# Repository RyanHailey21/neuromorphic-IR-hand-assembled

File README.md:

# Neuromorphic IR Event Sensor — Rev A-THT (hand-assembly)

All through-hole re-implementation of the Rev A neuromorphic IR event sensor: no SMD parts, solderable with a basic iron. Same architecture as the SMD design spec: 4 photodiodes → TIA → temporal adaptation → ON/OFF comparators → one-shots → 8 asynchronous 3.3 V spike outputs for the Tang Nano 20K.

- **Board:** 100 × 100 mm, 2 layers, 1.6 mm FR4, 0.3 mm min track, GND pour on both layers
- **Status:** ERC 0 · DRC 0 · schematic↔PCB parity 0 · 0 unconnected
- **Fab files:** `production/neuromorphic-ir-sensor-tht-revA-THT-gerbers.zip` (upload as-is to JLCPCB/PCBWay, bare board only)
- **BOM:** `production/neuromorphic-ir-sensor-tht-BOM.csv` · **Schematic:** `docs/schematic.pdf` · **Assembly drawing:** `docs/assembly_top.pdf`

## Changes from the SMD spec

| Function | SMD Rev A | Rev A-THT | Effect |
|---|---|---|---|
| TIA ×4 | OPA381 | 2× **MCP6022-I/P** (dual, DIP-8) | RF/CF unchanged (18k / 47 pF); ~188 kHz BW, large phase margin |
| Comparators ×8 | 4× TLV3202 | 4× **MCP6542-I/P** (dual, DIP-8) | ~4 µs response, irrelevant vs 2.2 ms adaptation |
| One-shots ×8 | 8× 74LVC1G123 | 4× **74HC123** (dual, DIP-16) | 18k / 12 nF ≈ 100 µs (K≈0.45) — tune on bench |
| VREF | REF3312 1.250 V | **LM385BZ-1.2** 1.235 V + 4.7k | Thresholds ≈ +40.6 / −39.7 mV |
| LED switch | AO3400A | **PN2222A** + 1k base | ~22 mA LED current with 82 Ω |
| Photodiodes | VBPW34FASR | **OSRAM BPW 34 F** (daylight filter) | Same die, THT |

The FPGA connector follows the spec (keyed 2×5: GND, 3V3, SPIKE_ON/OFF × 4). The AER / 2×10 pinout in the old README had no driving circuitry and was dropped.

## Connectors

| Ref | Pins |
|---|---|
| J1 FPGA (2×5 box) | 1 GND · 2 3V3 · 3 ON_TL · 4 OFF_TL · 5 ON_TR · 6 OFF_TR · 7 ON_BL · 8 OFF_BL · 9 ON_BR · 10 OFF_BR |
| J2 DEBUG | 1 GND · 2 VREF · 3–6 VPHOTO_TL/TR/BL/BR (via 100 Ω) |
| J3 LED_EN | 1 3V3 · 2 LED_EN · 3 GND — jumper 1-2 = LED on, 2-3 = off, or drive pin 2 from FPGA |
| J4 RAW_PROBE | 1 GND · 2–9 RAW_ON/OFF_TL, TR, BL, BR |
| J5 EVENT_PROBE | 1 GND · 2 3V3 · 3 3V3A · 4 VREF · 5 VTH_ON · 6 VTH_OFF · 7–10 VEVENT_TL/TR/BL/BR |

## Assembly notes

- Buy 6× DIP-8 and 4× DIP-16 sockets; fit ICs last.
- Solder lowest parts first: resistors → ceramic caps → sockets → TO-92 → electrolytics → headers → photodiodes/LED.
- **Polarity:** photodiode cathode (marked side) → square pad; LED1 cathode (flat) → square pad; electrolytic + marked on silk; U1/Q1 flat side per silk.
- R18–R21 (1 MΩ hysteresis) are **DNP** — fit only if comparators chatter.
- Tuning parts (adaptation R/C, one-shot R/C, thresholds, RLED) can be fitted in machined-pin socket strips for tool-free swapping.
- Keep the photodiode cluster area clear for the M12 lens housing.

## Regenerating (headless)

Everything is generated from `.companion/scripts/design.py` (netlist source of truth). With KiCad closed:

```bash
python .companion/scripts/gen_schematic.py --force
"C:/Program Files/KiCad/10.0/bin/python.exe" .companion/scripts/gen_pcb.py --force
python .companion/scripts/setup_rules.py
# autoroute (kicad-companion autoroute_board / Freerouting), then:
"C:/Program Files/KiCad/10.0/bin/python.exe" .companion/scripts/finalize_pcb.py
python .companion/scripts/setup_rules.py
```

Close KiCad before regenerating: it rewrites the `.kicad_pro` from memory on exit and drops the net classes.

## Open items

- Re-run SPICE with Microchip's MCP6022 / MCP6542 vendor models (not yet in the repo).
- Bench-trim the 74HC123 pulse width (K varies with supply voltage).
- The TIA input nets (photodiode + RF + CF) are autorouted at 22–36 mm total length, well above the spec's 2–8 mm photodiode→op-amp target. The op-amps sit back from the cluster to leave room for the lens housing. Worth a manual tidy-up in KiCad if noise turns out to be a problem on the bench.

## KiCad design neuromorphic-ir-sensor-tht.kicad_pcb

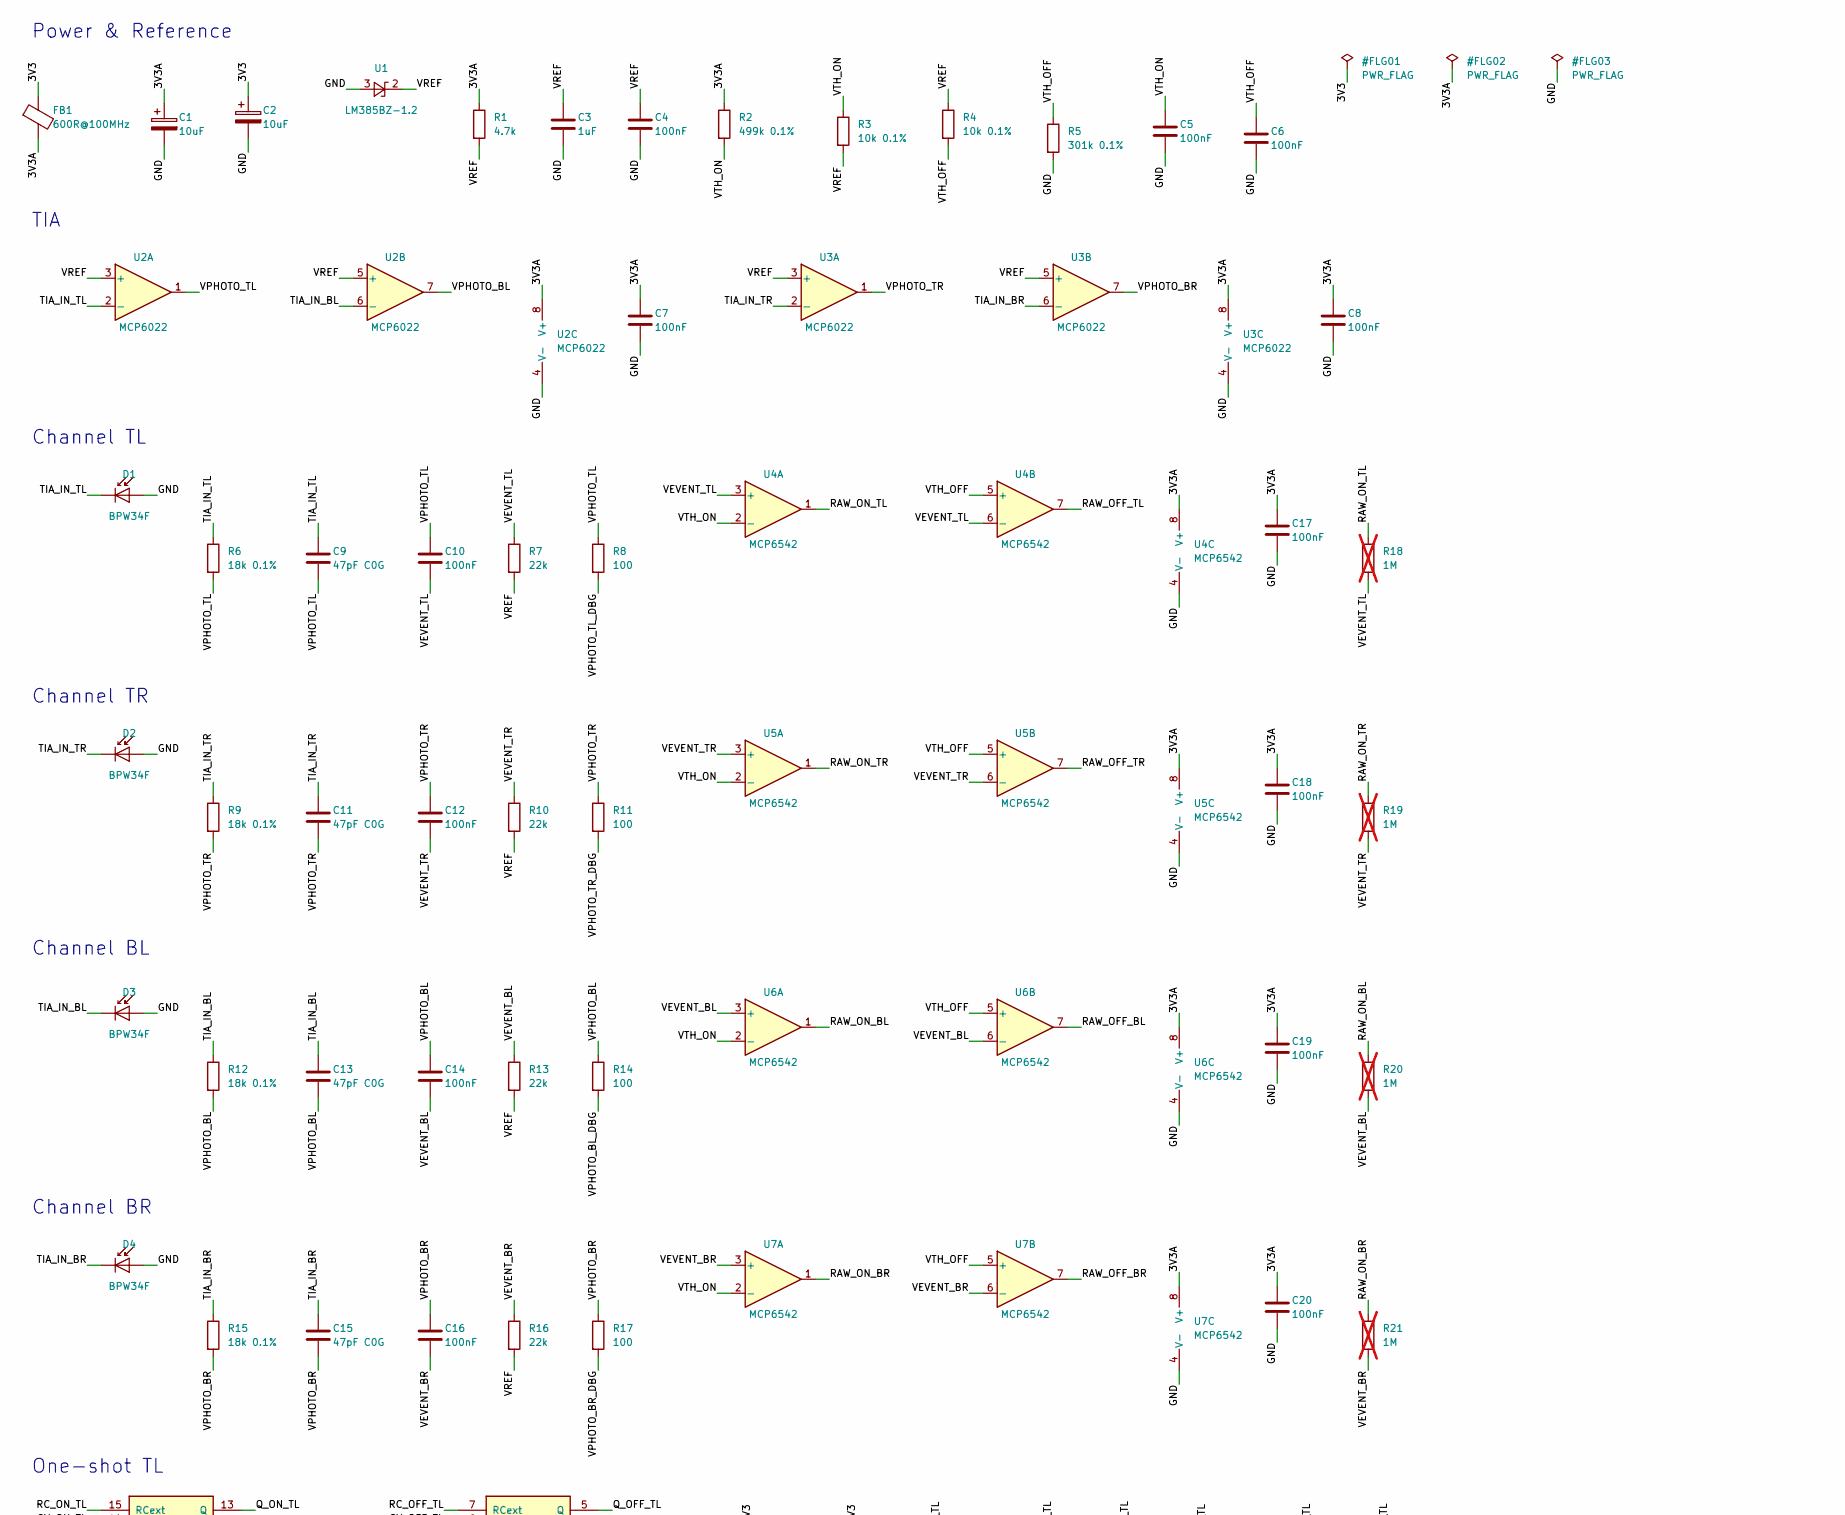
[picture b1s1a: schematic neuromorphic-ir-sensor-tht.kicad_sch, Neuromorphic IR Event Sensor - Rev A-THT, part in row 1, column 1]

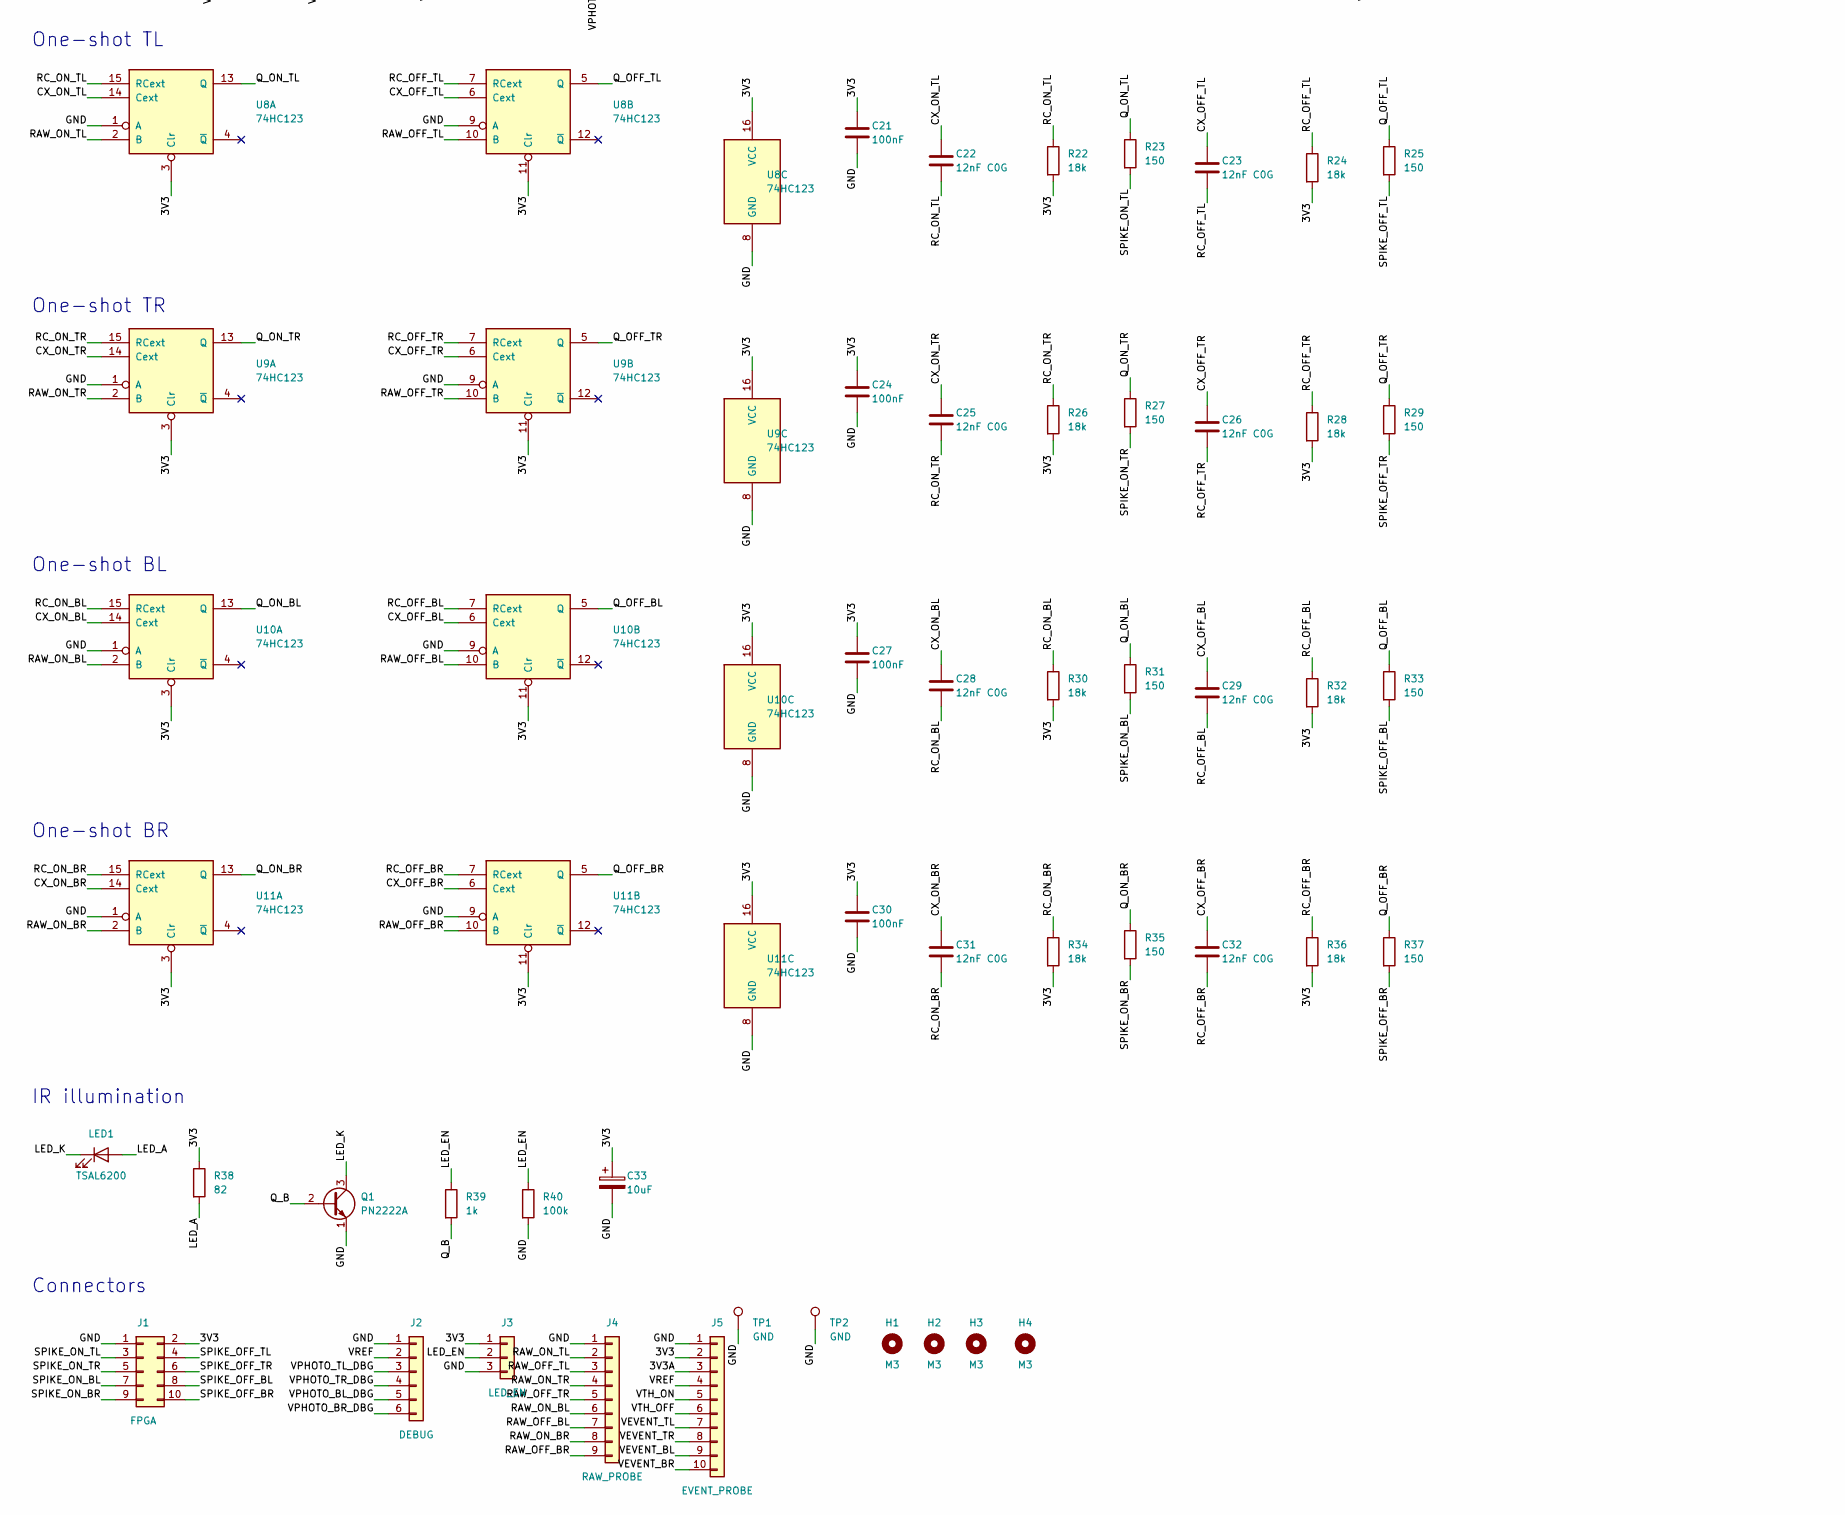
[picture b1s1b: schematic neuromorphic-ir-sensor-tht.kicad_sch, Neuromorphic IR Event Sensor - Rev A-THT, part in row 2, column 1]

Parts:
C1, C2, C33: 10uF; CP_Radial_D5.0mm_P2.00mm; MPN 10uF 16V radial electrolytic
C3: 1uF; C_Disc_D5.0mm_W2.5mm_P5.00mm; MPN 1uF X7R radial
C4, C5, C6, C7, C8, C10, C12, C14, C16, C17, C18, C19, C20, C21, C24, C27, C30: 100nF; C_Disc_D5.0mm_W2.5mm_P5.00mm
C9, C11, C13, C15: 47pF C0G; C_Disc_D5.0mm_W2.5mm_P5.00mm; MPN 47pF C0G radial
C22, C23, C25, C26, C28, C29, C31, C32: 12nF C0G; C_Disc_D5.0mm_W2.5mm_P5.00mm; MPN 12nF C0G radial or film
D1, D2, D3, D4: BPW34F; Osram_DIL2_4.3x4.65mm_P5.08mm; MPN ams OSRAM BPW 34 F (THT, daylight filte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
FB1: 600R@100MHz; L_Axial_L5.3mm_D2.2mm_P7.62mm_Horizontal_Vishay_IM-1; MPN Axial ferrite bead (e.g. Fair-Rite 2743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
H1, H2, H3, H4: M3; MountingHole_3.2mm_M3
J1: FPGA; IDC-Header_2x05_P2.54mm_Vertical; MPN 2x5 2.54mm shrouded box header
J2: DEBUG; PinHeader_1x06_P2.54mm_Vertical
J3: LED_EN; PinHeader_1x03_P2.54mm_Vertical
J4: RAW_PROBE; PinHeader_1x09_P2.54mm_Vertical
J5: EVENT_PROBE; PinHeader_1x10_P2.54mm_Vertical
LED1: TSAL6200; LED_D5.0mm_IRGrey; MPN Vishay TSAL6200
Q1: PN2222A; TO-92_Inline_Wide; MPN PN2222A
R1: 4.7k; R_Axial_DIN0207_L6.3mm_D2.5mm_P7.62mm_Horizontal
R2: 499k 0.1%; R_Axial_DIN0207_L6.3mm_D2.5mm_P7.62mm_Horizontal
R3, R4: 10k 0.1%; R_Axial_DIN0207_L6.3mm_D2.5mm_P7.62mm_Horizontal
R5: 301k 0.1%; R_Axial_DIN0207_L6.3mm_D2.5mm_P7.62mm_Horizontal
R6, R9, R12, R15: 18k 0.1%; R_Axial_DIN0207_L6.3mm_D2.5mm_P7.62mm_Horizontal
R7, R10, R13, R16: 22k; R_Axial_DIN0207_L6.3mm_D2.5mm_P7.62mm_Horizontal
R8, R11, R14, R17: 100; R_Axial_DIN0207_L6.3mm_D2.5mm_P7.62mm_Horizontal
R18, R19, R20, R21: 1M; R_Axial_DIN0207_L6.3mm_D2.5mm_P7.62mm_Horizontal; not fitted
R22, R24, R26, R28, R30, R32, R34, R36: 18k; R_Axial_DIN0207_L6.3mm_D2.5mm_P7.62mm_Horizontal
R23, R25, R27, R29, R31, R33, R35, R37: 150; R_Axial_DIN0207_L6.3mm_D2.5mm_P7.62mm_Horizontal
R38: 82; R_Axial_DIN0207_L6.3mm_D2.5mm_P7.62mm_Horizontal
R39: 1k; R_Axial_DIN0207_L6.3mm_D2.5mm_P7.62mm_Horizontal
R40: 100k; R_Axial_DIN0207_L6.3mm_D2.5mm_P7.62mm_Horizontal
TP1, TP2: GND; TestPoint_Keystone_5000-5004_Miniature
U1: LM385BZ-1.2; TO-92_Inline_Wide; MPN LM385BZ-1.2
U2, U3: MCP6022; DIP-8_W7.62mm_Socket; MPN MCP6022-I/P
U4, U5, U6, U7: MCP6542; DIP-8_W7.62mm_Socket; MPN MCP6542-I/P
U8, U9, U10, U11: 74HC123; DIP-16_W7.62mm_Socket; MPN 74HC123 (SN74HC123N / 74HC123N)

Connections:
/3V3: C2.1, C21.1, C24.1, C27.1, C30.1, C33.1, FB1.1, J1.2, J3.1, J5.2, R22.2, R24.2, R26.2, R28.2, R30.2, R32.2, R34.2, R36.2, R38.1, U8.3 (Clr), U8.11 (Clr), U8.16 (VCC), U9.3 (Clr), U9.11 (Clr), U9.16 (VCC), U10.3 (Clr), U10.11 (Clr), U10.16 (VCC), U11.3 (Clr), U11.11 (Clr), U11.16 (VCC)
/3V3A: C1.1, C7.1, C8.1, C17.1, C18.1, C19.1, C20.1, FB1.2, J5.3, R1.1, R2.1, U2.8 (V+), U3.8 (V+), U4.8 (V+), U5.8 (V+), U6.8 (V+), U7.8 (V+)
/CX_OFF_BL: C29.1, U10.6 (Cext)
/CX_OFF_BR: C32.1, U11.6 (Cext)
/CX_OFF_TL: C23.1, U8.6 (Cext)
/CX_OFF_TR: C26.1, U9.6 (Cext)
/CX_ON_BL: C28.1, U10.14 (Cext)
/CX_ON_BR: C31.1, U11.14 (Cext)
/CX_ON_TL: C22.1, U8.14 (Cext)
/CX_ON_TR: C25.1, U9.14 (Cext)
/GND: C1.2, C2.2, C3.2, C4.2, C5.2, C6.2, C7.2, C8.2, C17.2, C18.2, C19.2, C20.2, C21.2, C24.2, C27.2, C30.2, C33.2, D1.2 (A), D2.2 (A), D3.2 (A), D4.2 (A), J1.1, J2.1, J3.3, J4.1, J5.1, Q1.1 (E), R5.2, R40.2, TP1.1, TP2.1, U1.3 (A), U2.4 (V-), U3.4 (V-), U4.4 (V-), U5.4 (V-), U6.4 (V-), U7.4 (V-), U8.1 (A), U8.8 (GND), U8.9 (A), U9.1 (A), U9.8 (GND), U9.9 (A), U10.1 (A), U10.8 (GND), U10.9 (A), U11.1 (A), U11.8 (GND), U11.9 (A)
/LED_A: LED1.2 (A), R38.2
/LED_EN: J3.2, R39.1, R40.1
/LED_K: LED1.1 (K), Q1.3 (C)
/Q_B: Q1.2 (B), R39.2
/Q_OFF_BL: R33.1, U10.5 (Q)
/Q_OFF_BR: R37.1, U11.5 (Q)
/Q_OFF_TL: R25.1, U8.5 (Q)
/Q_OFF_TR: R29.1, U9.5 (Q)
/Q_ON_BL: R31.1, U10.13 (Q)
/Q_ON_BR: R35.1, U11.13 (Q)
/Q_ON_TL: R23.1, U8.13 (Q)
/Q_ON_TR: R27.1, U9.13 (Q)
/RAW_OFF_BL: J4.7, U6.7, U10.10 (B)
/RAW_OFF_BR: J4.9, U7.7, U11.10 (B)
/RAW_OFF_TL: J4.3, U4.7, U8.10 (B)
/RAW_OFF_TR: J4.5, U5.7, U9.10 (B)
/RAW_ON_BL: J4.6, R20.1, U6.1, U10.2 (B)
/RAW_ON_BR: J4.8, R21.1, U7.1, U11.2 (B)
/RAW_ON_TL: J4.2, R18.1, U4.1, U8.2 (B)
/RAW_ON_TR: J4.4, R19.1, U5.1, U9.2 (B)
/RC_OFF_BL: C29.2, R32.1, U10.7 (RCext)
/RC_OFF_BR: C32.2, R36.1, U11.7 (RCext)
/RC_OFF_TL: C23.2, R24.1, U8.7 (RCext)
/RC_OFF_TR: C26.2, R28.1, U9.7 (RCext)
/RC_ON_BL: C28.2, R30.1, U10.15 (RCext)
/RC_ON_BR: C31.2, R34.1, U11.15 (RCext)
/RC_ON_TL: C22.2, R22.1, U8.15 (RCext)
/RC_ON_TR: C25.2, R26.1, U9.15 (RCext)
/SPIKE_OFF_BL: J1.8, R33.2
/SPIKE_OFF_BR: J1.10, R37.2
/SPIKE_OFF_TL: J1.4, R25.2
/SPIKE_OFF_TR: J1.6, R29.2
/SPIKE_ON_BL: J1.7, R31.2
/SPIKE_ON_BR: J1.9, R35.2
/SPIKE_ON_TL: J1.3, R23.2
/SPIKE_ON_TR: J1.5, R27.2
/TIA_IN_BL: C13.1, D3.1 (K), R12.1, U2.6 (-)
/TIA_IN_BR: C15.1, D4.1 (K), R15.1, U3.6 (-)
/TIA_IN_TL: C9.1, D1.1 (K), R6.1, U2.2 (-)
/TIA_IN_TR: C11.1, D2.1 (K), R9.1, U3.2 (-)
/VEVENT_BL: C14.2, J5.9, R13.1, R20.2, U6.3 (+), U6.6 (-)
/VEVENT_BR: C16.2, J5.10, R16.1, R21.2, U7.3 (+), U7.6 (-)
/VEVENT_TL: C10.2, J5.7, R7.1, R18.2, U4.3 (+), U4.6 (-)
/VEVENT_TR: C12.2, J5.8, R10.1, R19.2, U5.3 (+), U5.6 (-)
/VPHOTO_BL: C13.2, C14.1, R12.2, R14.1, U2.7
/VPHOTO_BL_DBG: J2.5, R14.2
/VPHOTO_BR: C15.2, C16.1, R15.2, R17.1, U3.7
/VPHOTO_BR_DBG: J2.6, R17.2
/VPHOTO_TL: C9.2, C10.1, R6.2, R8.1, U2.1
/VPHOTO_TL_DBG: J2.3, R8.2
/VPHOTO_TR: C11.2, C12.1, R9.2, R11.1, U3.1
/VPHOTO_TR_DBG: J2.4, R11.2
/VREF: C3.1, C4.1, J2.2, J5.4, R1.2, R3.2, R4.1, R7.2, R10.2, R13.2, R16.2, U1.2 (K), U2.3 (+), U2.5 (+), U3.3 (+), U3.5 (+)
/VTH_OFF: C6.1, J5.6, R4.2, R5.1, U4.5 (+), U5.5 (+), U6.5 (+), U7.5 (+)
/VTH_ON: C5.1, J5.5, R2.2, R3.1, U4.2 (-), U5.2 (-), U6.2 (-), U7.2 (-)

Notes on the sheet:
Power & Reference
TIA
Channel TL
Channel TR
Channel BL
Channel BR
One-shot TL
One-shot TR
One-shot BL
One-shot BR
IR illumination
Connectors
Neuromorphic IR Event Sensor - Rev A-THT (all through-hole, hand-assemblable). Single source of truth for the netlist. gen_schematic.py turns this into the KiCad schematic; the PCB is then populated from the schematic netlist. Deviations from docs/DESIGN_SPECIFICATION.md (SMD Rev A), forced by THT 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

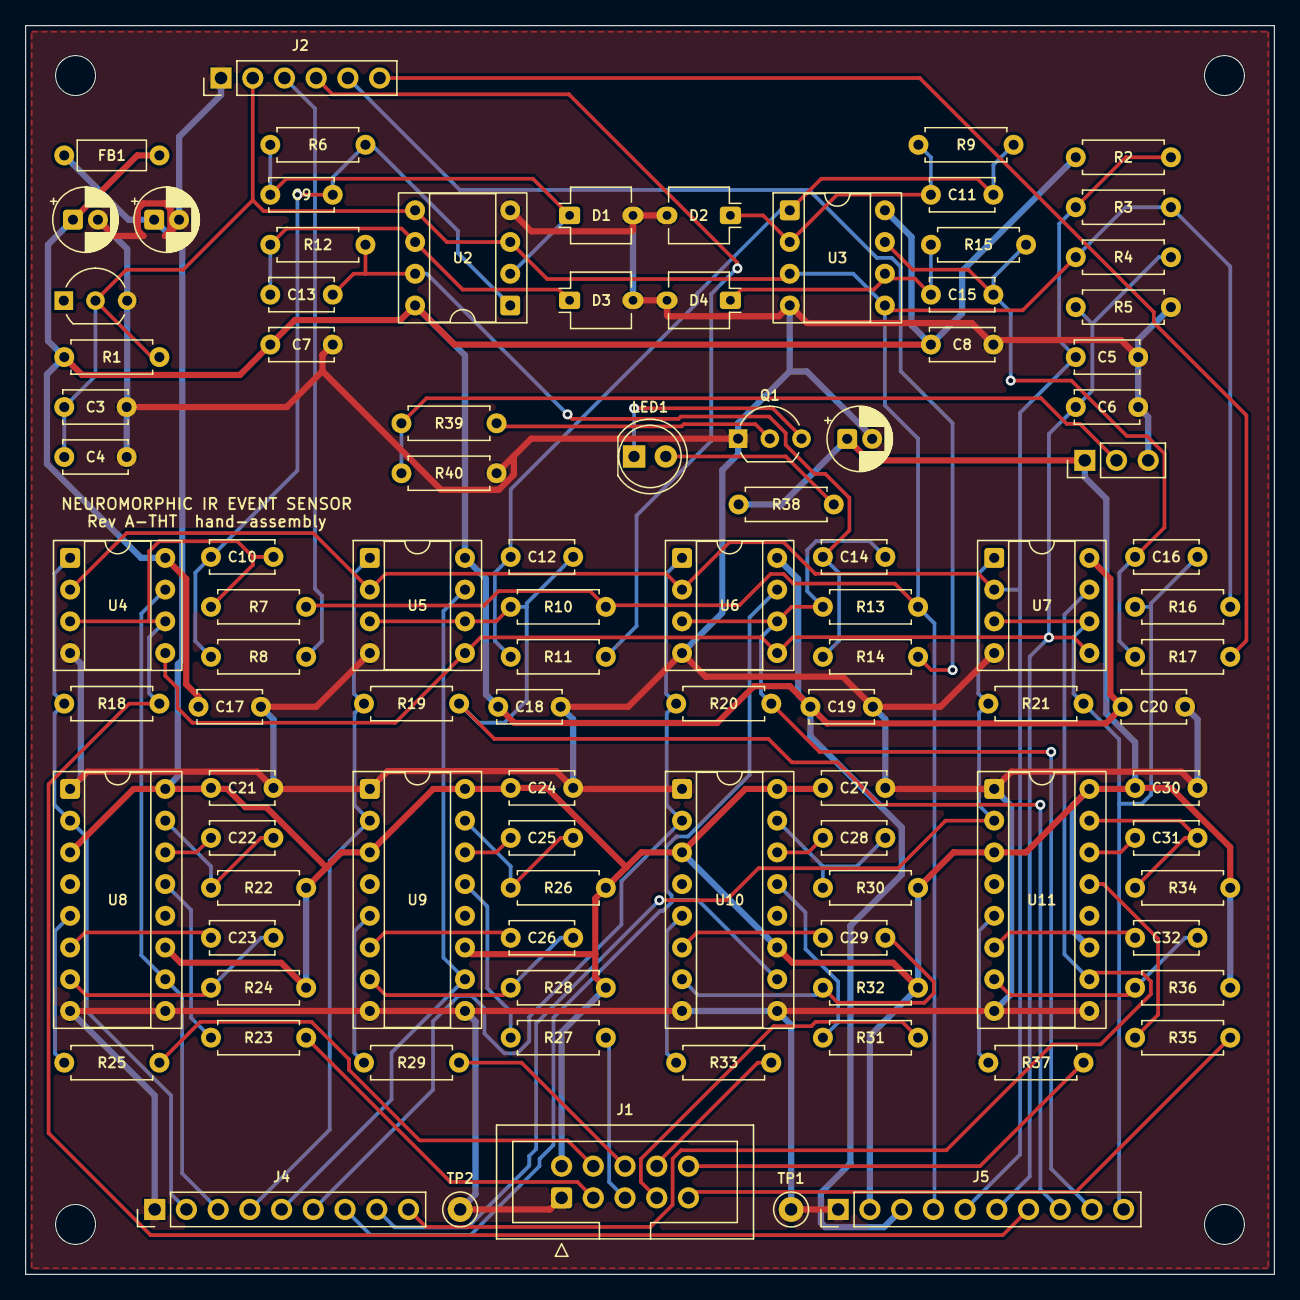
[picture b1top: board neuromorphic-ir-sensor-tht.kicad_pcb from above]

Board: 2 copper layers, 100.0 x 100.0 mm, 102 parts (0 on the bottom side), 66 nets.

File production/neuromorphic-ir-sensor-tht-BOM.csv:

"Qty","Value","References","Part / MPN","Function","Footprint","DNP"
"3","10uF","C1,C2,C33","10uF 16V radial electrolytic","Analog bulk,LED local bulk,Logic / one-shot bulk","Capacitor_THT:CP_Radial_D5.0mm_P2.00mm",""
"1","1uF","C3","1uF X7R radial","Reference decoupling","Capacitor_THT:C_Disc_D5.0mm_W2.5mm_P5.00mm",""
"17","100nF","C4-C8,C10,C12,C14,C16-C21,C24,C27,C30","","Adaptation CA (swap 47n/220n),Reference decoupling,Threshold filter,U10 decoupling,U11 decoupling,U2 decoupling,U3 decoupling,U4 decoupling,U5 decoupling,U6 decoupling,U7 decoupling,U8 decoupling,U9 decoupling","Capacitor_THT:C_Disc_D5.0mm_W2.5mm_P5.00mm",""
"4","47pF C0G","C9,C11,C13,C15","47pF C0G radial","TIA feedback CF","Capacitor_THT:C_Disc_D5.0mm_W2.5mm_P5.00mm",""
"8","12nF C0G","C22,C23,C25,C26,C28,C29,C31,C32","12nF C0G radial or film","One-shot timing C","Capacitor_THT:C_Disc_D5.0mm_W2.5mm_P5.00mm",""
"4","BPW34F","D1-D4","ams OSRAM BPW 34 F (THT, daylight filter); alt Vishay BPW34","IR photodiode BL (cathode to TIA input),IR photodiode BR (cathode to TIA input),IR photodiode TL (cathode to TIA input),IR photodiode TR (cathode to TIA input)","OptoDevice:Osram_DIL2_4.3x4.65mm_P5.08mm",""
"1","600R@100MHz","FB1","Axial ferrite bead (e.g. Fair-Rite 2743001112)","Analog rail filter bead","Inductor_THT:L_Axial_L5.3mm_D2.2mm_P7.62mm_Horizontal_Vishay_IM-1",""
"1","FPGA","J1","2x5 2.54mm shrouded box header","Keyed 2x5 event header to Tang Nano 20K","Connector_IDC:IDC-Header_2x05_P2.54mm_Vertical",""
"1","DEBUG","J2","","Analog debug header","Connector_PinHeader_2.54mm:PinHeader_1x06_P2.54mm_Vertical",""
"1","LED_EN","J3","","Jumper 1-2 = LED on, 2-3 = off, or drive pin 2 from FPGA","Connector_PinHeader_2.54mm:PinHeader_1x03_P2.54mm_Vertical",""
"1","RAW_PROBE","J4","","Raw comparator probe header","Connector_PinHeader_2.54mm:PinHeader_1x09_P2.54mm_Vertical",""
"1","EVENT_PROBE","J5","","Rail / threshold / event-node probe header","Connector_PinHeader_2.54mm:PinHeader_1x10_P2.54mm_Vertical",""
"1","TSAL6200","LED1","Vishay TSAL6200","940 nm IR emitter","LED_THT:LED_D5.0mm_IRGrey",""
"1","PN2222A","Q1","PN2222A","LED low-side switch","Package_TO_SOT_THT:TO-92_Inline_Wide",""
"1","4.7k","R1","","Reference bias ~0.44 mA","Resistor_THT:R_Axial_DIN0207_L6.3mm_D2.5mm_P7.62mm_Horizontal",""
"1","499k 0.1%","R2","","ON threshold upper","Resistor_THT:R_Axial_DIN0207_L6.3mm_D2.5mm_P7.62mm_Horizontal",""
"2","10k 0.1%","R3,R4","","OFF threshold upper,ON threshold lower","Resistor_THT:R_Axial_DIN0207_L6.3mm_D2.5mm_P7.62mm_Horizontal",""
"1","301k 0.1%","R5","","OFF threshold lower","Resistor_THT:R_Axial_DIN0207_L6.3mm_D2.5mm_P7.62mm_Horizontal",""
"4","18k 0.1%","R6,R9,R12,R15","","TIA feedback RF","Resistor_THT:R_Axial_DIN0207_L6.3mm_D2.5mm_P7.62mm_Horizontal",""
"4","22k","R7,R10,R13,R16","","Adaptation RA (swap 10k/47k)","Resistor_THT:R_Axial_DIN0207_L6.3mm_D2.5mm_P7.62mm_Horizontal",""
"4","100","R8,R11,R14,R17","","Debug header series R","Resistor_THT:R_Axial_DIN0207_L6.3mm_D2.5mm_P7.62mm_Horizontal",""
"4","1M","R18-R21","","Optional ON hysteresis (DNP)","Resistor_THT:R_Axial_DIN0207_L6.3mm_D2.5mm_P7.62mm_Horizontal","DNP"
"8","18k","R22,R24,R26,R28,R30,R32,R34,R36","","One-shot timing R (~100 us)","Resistor_THT:R_Axial_DIN0207_L6.3mm_D2.5mm_P7.62mm_Horizontal",""
"8","150","R23,R25,R27,R29,R31,R33,R35,R37","","Spike series R","Resistor_THT:R_Axial_DIN0207_L6.3mm_D2.5mm_P7.62mm_Horizontal",""
"1","82","R38","","LED current (~22 mA) - tuning 68/100/150","Resistor_THT:R_Axial_DIN0207_L6.3mm_D2.5mm_P7.62mm_Horizontal",""
"1","1k","R39","","Base resistor","Resistor_THT:R_Axial_DIN0207_L6.3mm_D2.5mm_P7.62mm_Horizontal",""
"1","100k","R40","","LED_EN pulldown","Resistor_THT:R_Axial_DIN0207_L6.3mm_D2.5mm_P7.62mm_Horizontal",""
"2","GND","TP1,TP2","","Scope ground loop","TestPoint:TestPoint_Keystone_5000-5004_Miniature",""
"1","LM385BZ-1.2","U1","LM385BZ-1.2","1.235 V shunt reference (VREF)","Package_TO_SOT_THT:TO-92_Inline_Wide",""
"2","MCP6022","U2,U3","MCP6022-I/P","Dual RRIO CMOS op-amp (TIA)","Package_DIP:DIP-8_W7.62mm_Socket",""
"4","MCP6542","U4-U7","MCP6542-I/P","Dual push-pull comparator, ON (A) / OFF (B)","Package_DIP:DIP-8_W7.62mm_Socket",""
"4","74HC123","U8-U11","74HC123 (SN74HC123N / 74HC123N)","Dual retriggerable monostable, ON (A) / OFF (B)","Package_DIP:DIP-16_W7.62mm_Socket",""

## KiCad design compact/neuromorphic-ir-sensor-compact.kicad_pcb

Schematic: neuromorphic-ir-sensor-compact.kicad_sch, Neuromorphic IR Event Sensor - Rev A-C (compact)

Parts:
C1, C2, C38: 10uF; C_0402_1005Metric; MPN GRM155R60J106ME15D
C3, C5, C6, C7, C8, C9, C11, C13, C15, C17, C18, C19, C20, C21, C22, C24, C26, C28, C30, C32, C34, C36: 100nF; C_0201_0603Metric; MPN GRM033R71A104KA01D
C4: 1uF; C_0201_0603Metric; MPN GRM033R60J105MEA2D
C10, C12, C14, C16: 47pF; C_0201_0603Metric; MPN GRM0335C1H470JA01D
C23, C25, C27, C29, C31, C33, C35, C37: 1nF; C_0201_0603Metric; MPN GRM0335C1H102JA01D
D1, D2, D3, D4: BPW 34 FAS; Osram_BPW34S-SMD; MPN BPW 34 FAS
FB1: 600R@100MHz; L_0402_1005Metric; MPN BLM15AG601SN1D
H1, H2: M2; MountingHole_2.2mm_M2
J1: FPGA; PinHeader_2x05_P1.27mm_Vertical_SMD; MPN 2x5 1.27mm SMD pin header, gold
JP1: LED_EN; SolderJumper-3_P1.3mm_Bridged12_Pad1.0x1.5mm
LED1: TSAL6200; LED_D5.0mm_IRGrey; MPN TSAL6200
Q1: AO3400A; SOT-23; MPN AO3400A
R1: 499k 0.1%; R_0402_1005Metric; MPN 499k 0.1% 0402 thin film
R2, R3: 10k 0.1%; R_0402_1005Metric; MPN 10k 0.1% 0402 thin film
R4: 301k 0.1%; R_0402_1005Metric; MPN 301k 0.1% 0402 thin film
R5, R7, R9, R11: 18k 0.1%; R_0201_0603Metric; MPN 18k 0.1% 0201 thin film
R6, R8, R10, R12: 22k; R_0201_0603Metric; MPN 22k 0201 thick film 1%
R13, R14, R15, R16: 1M; R_0201_0603Metric; MPN 1M 0201 thick film 1%; not fitted
R17, R19, R21, R23, R25, R27, R29, R31, R35: 100k; R_0201_0603Metric; MPN 100k 0201 thick film 1%
R18, R20, R22, R24, R26, R28, R30, R32: 150; R_0201_0603Metric; MPN 150 0201 thick film 1%
R33: 82; R_0402_1005Metric; MPN 82R 0402 1% (62.5 mW)
R34: 100; R_0201_0603Metric; MPN 100 0201 thick film 1%
TP1: 3V3A; TestPoint_Pad_D1.0mm
TP2: GND; TestPoint_Pad_D1.0mm
TP3: VREF; TestPoint_Pad_D1.0mm
TP4: VTH_ON; TestPoint_Pad_D1.0mm
TP5: VTH_OFF; TestPoint_Pad_D1.0mm
TP6: LED_EN; TestPoint_Pad_D1.0mm
TP7: VPHOTO_TL; TestPoint_Pad_D1.0mm
TP8: VPHOTO_TR; TestPoint_Pad_D1.0mm
TP9: VPHOTO_BL; TestPoint_Pad_D1.0mm
TP10: VPHOTO_BR; TestPoint_Pad_D1.0mm
TP11: VEVENT_TL; TestPoint_Pad_D1.0mm
TP12: VEVENT_TR; TestPoint_Pad_D1.0mm
TP13: VEVENT_BL; TestPoint_Pad_D1.0mm
TP14: VEVENT_BR; TestPoint_Pad_D1.0mm
TP15: RAW_ON_TL; TestPoint_Pad_D1.0mm
TP16: RAW_OFF_TL; TestPoint_Pad_D1.0mm
TP17: RAW_ON_TR; TestPoint_Pad_D1.0mm
TP18: RAW_OFF_TR; TestPoint_Pad_D1.0mm
TP19: RAW_ON_BL; TestPoint_Pad_D1.0mm
TP20: RAW_OFF_BL; TestPoint_Pad_D1.0mm
TP21: RAW_ON_BR; TestPoint_Pad_D1.0mm
TP22: RAW_OFF_BR; TestPoint_Pad_D1.0mm
U1: REF3312AIDCKR; SOT-323_SC-70; MPN REF3312AIDCKR
U2, U3: OPA2381AIDRBR; VSON-8-1EP_3x3mm_P0.65mm_EP1.65x2.4mm; MPN OPA2381AIDRBR
U4, U5, U6, U7: TLV3202AIDGKR; VSSOP-8_3x3mm_P0.65mm; MPN TLV3202AIDGKR
U8, U9, U10, U11, U12, U13, U14, U15: SN74LVC1G123DCUR; VSSOP-8_2.3x2mm_P0.5mm; MPN SN74LVC1G123DCUR

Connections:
/3V3: C2.1, C22.1, C24.1, C26.1, C28.1, C30.1, C32.1, C34.1, C36.1, C38.1, FB1.1, J1.2, JP1.1 (A), R17.2, R19.2, R21.2, R23.2, R25.2, R27.2, R29.2, R31.2, R33.1, U8.3 (~CLR), U8.8 (VCC), U9.3 (~CLR), U9.8 (VCC), U10.3 (~CLR), U10.8 (VCC), U11.3 (~CLR), U11.8 (VCC), U12.3 (~CLR), U12.8 (VCC), U13.3 (~CLR), U13.8 (VCC), U14.3 (~CLR), U14.8 (VCC), U15.3 (~CLR), U15.8 (VCC)
/3V3A: C1.1, C3.1, C8.1, C9.1, C18.1, C19.1, C20.1, C21.1, FB1.2, R1.1, TP1.1, U1.1 (IN), U2.8 (V+), U3.8 (V+), U4.8 (V+), U5.8 (V+), U6.8 (V+), U7.8 (V+)
/CX_OFF_BL: C33.1, U13.6 (Cext)
/CX_OFF_BR: C37.1, U15.6 (Cext)
/CX_OFF_TL: C25.1, U9.6 (Cext)
/CX_OFF_TR: C29.1, U11.6 (Cext)
/CX_ON_BL: C31.1, U12.6 (Cext)
/CX_ON_BR: C35.1, U14.6 (Cext)
/CX_ON_TL: C23.1, U8.6 (Cext)
/CX_ON_TR: C27.1, U10.6 (Cext)
/GND: C1.2, C2.2, C3.2, C4.2, C5.2, C6.2, C7.2, C8.2, C9.2, C18.2, C19.2, C20.2, C21.2, C22.2, C24.2, C26.2, C28.2, C30.2, C32.2, C34.2, C36.2, C38.2, D1.2 (A), D2.2 (A), D3.2 (A), D4.2 (A), J1.1, JP1.3 (B), Q1.2 (S), R4.2, R35.2, TP2.1, U1.3 (GND), U2.4 (V-), U2.9 (EP), U3.4 (V-), U3.9 (EP), U4.4 (V-), U5.4 (V-), U6.4 (V-), U7.4 (V-), U8.1 (~A), U8.4 (GND), U9.1 (~A), U9.4 (GND), U10.1 (~A), U10.4 (GND), U11.1 (~A), U11.4 (GND), U12.1 (~A), U12.4 (GND), U13.1 (~A), U13.4 (GND), U14.1 (~A), U14.4 (GND), U15.1 (~A), U15.4 (GND)
/LED_A: LED1.2 (A), R33.2
/LED_EN: JP1.2 (C), R34.1, TP6.1
/LED_K: LED1.1 (K), Q1.3 (D)
/Q_G: Q1.1 (G), R34.2, R35.1
/Q_OFF_BL: R28.1, U13.5 (Q)
/Q_OFF_BR: R32.1, U15.5 (Q)
/Q_OFF_TL: R20.1, U9.5 (Q)
/Q_OFF_TR: R24.1, U11.5 (Q)
/Q_ON_BL: R26.1, U12.5 (Q)
/Q_ON_BR: R30.1, U14.5 (Q)
/Q_ON_TL: R18.1, U8.5 (Q)
/Q_ON_TR: R22.1, U10.5 (Q)
/RAW_OFF_BL: TP20.1, U6.7, U13.2 (B)
/RAW_OFF_BR: TP22.1, U7.7, U15.2 (B)
/RAW_OFF_TL: TP16.1, U4.7, U9.2 (B)
/RAW_OFF_TR: TP18.1, U5.7, U11.2 (B)
/RAW_ON_BL: R15.1, TP19.1, U6.1, U12.2 (B)
/RAW_ON_BR: R16.1, TP21.1, U7.1, U14.2 (B)
/RAW_ON_TL: R13.1, TP15.1, U4.1, U8.2 (B)
/RAW_ON_TR: R14.1, TP17.1, U5.1, U10.2 (B)
/RC_OFF_BL: C33.2, R27.1, U13.7 (RCext)
/RC_OFF_BR: C37.2, R31.1, U15.7 (RCext)
/RC_OFF_TL: C25.2, R19.1, U9.7 (RCext)
/RC_OFF_TR: C29.2, R23.1, U11.7 (RCext)
/RC_ON_BL: C31.2, R25.1, U12.7 (RCext)
/RC_ON_BR: C35.2, R29.1, U14.7 (RCext)
/RC_ON_TL: C23.2, R17.1, U8.7 (RCext)
/RC_ON_TR: C27.2, R21.1, U10.7 (RCext)
/SPIKE_OFF_BL: J1.8, R28.2
/SPIKE_OFF_BR: J1.10, R32.2
/SPIKE_OFF_TL: J1.4, R20.2
/SPIKE_OFF_TR: J1.6, R24.2
/SPIKE_ON_BL: J1.7, R26.2
/SPIKE_ON_BR: J1.9, R30.2
/SPIKE_ON_TL: J1.3, R18.2
/SPIKE_ON_TR: J1.5, R22.2
/TIA_IN_BL: C14.1, D3.1 (K), R9.1, U2.6 (-)
/TIA_IN_BR: C16.1, D4.1 (K), R11.1, U3.6 (-)
/TIA_IN_TL: C10.1, D1.1 (K), R5.1, U2.2 (-)
/TIA_IN_TR: C12.1, D2.1 (K), R7.1, U3.2 (-)
/VEVENT_BL: C15.2, R10.1, R15.2, TP13.1, U6.3 (+), U6.6 (-)
/VEVENT_BR: C17.2, R12.1, R16.2, TP14.1, U7.3 (+), U7.6 (-)
/VEVENT_TL: C11.2, R6.1, R13.2, TP11.1, U4.3 (+), U4.6 (-)
/VEVENT_TR: C13.2, R8.1, R14.2, TP12.1, U5.3 (+), U5.6 (-)
/VPHOTO_BL: C14.2, C15.1, R9.2, TP9.1, U2.7
/VPHOTO_BR: C16.2, C17.1, R11.2, TP10.1, U3.7
/VPHOTO_TL: C10.2, C11.1, R5.2, TP7.1, U2.1
/VPHOTO_TR: C12.2, C13.1, R7.2, TP8.1, U3.1
/VREF: C4.1, C5.1, R2.2, R3.1, R6.2, R8.2, R10.2, R12.2, TP3.1, U1.2 (OUT), U2.3 (+), U2.5 (+), U3.3 (+), U3.5 (+)
/VTH_OFF: C7.1, R3.2, R4.1, TP5.1, U4.5 (+), U5.5 (+), U6.5 (+), U7.5 (+)
/VTH_ON: C6.1, R1.2, R2.1, TP4.1, U4.2 (-), U5.2 (-), U6.2 (-), U7.2 (-)

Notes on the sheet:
Power & Reference
Photodiodes
TIA
Channel TL
Channel TR
Channel BL
Channel BR
One-shot TL
One-shot TR
One-shot BL
One-shot BR
IR illumination
Connectors
Test pads
Mechanical
Power flags
Neuromorphic IR Event Sensor - Rev A-C (compact, PCBWay-assembled). Smallest-footprint build of the Rev A spec. Writes compact/design/spec.json for kicad-companion's generate_schematic. Changes vs the SMD spec (docs/DESIGN_SPECIFICATION.md): OPA381 x4 (MSOP) -> OPA2381AIDRBR x2 (same amplifier, dua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

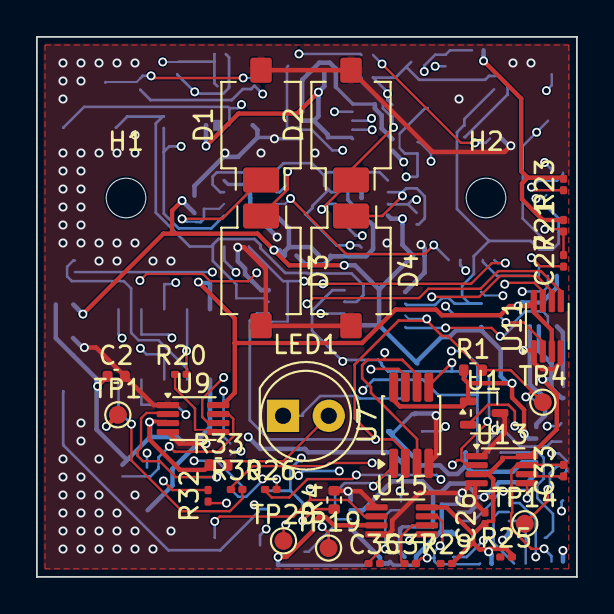
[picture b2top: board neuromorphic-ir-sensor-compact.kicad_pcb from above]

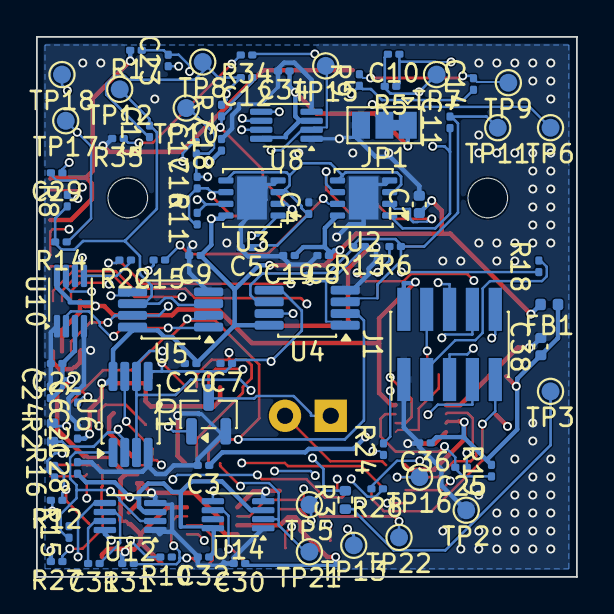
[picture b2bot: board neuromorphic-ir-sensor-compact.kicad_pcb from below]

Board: 4 copper layers, 30.0 x 30.0 mm, 121 parts (86 on the bottom side), 62 nets.
